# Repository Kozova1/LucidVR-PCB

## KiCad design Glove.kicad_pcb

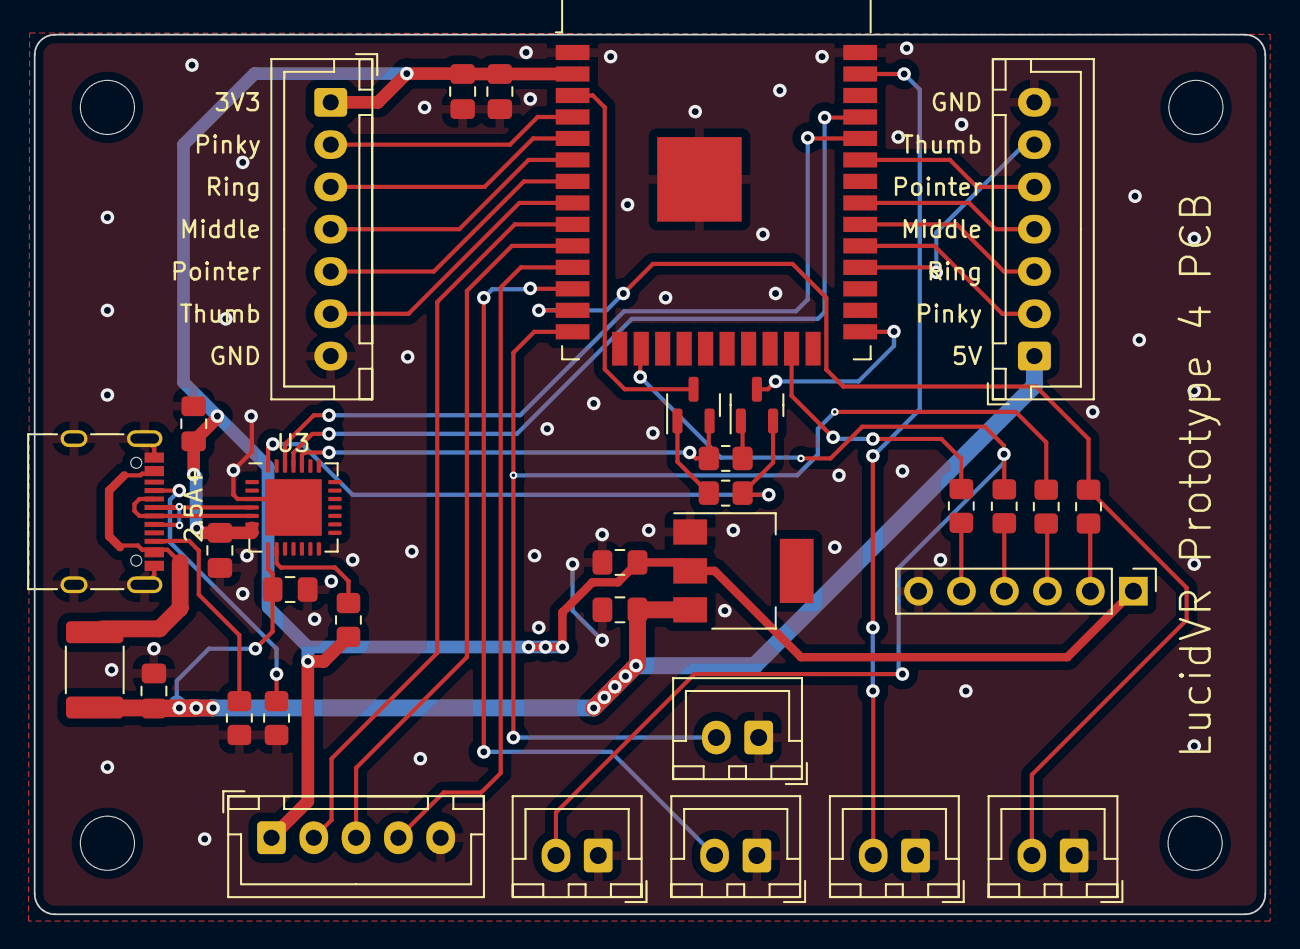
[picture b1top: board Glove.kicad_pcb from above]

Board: 2 copper layers, 72.8 x 52.0 mm, 33 parts (0 on the bottom side), 40 nets.

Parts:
BTN_A1: Button A; JST_XH_B2B-XH-A_1x02_P2.50mm_Vertical
BTN_B1: Button B; JST_XH_B2B-XH-A_1x02_P2.50mm_Vertical
BTN_Grab1: Grab; JST_XH_B2B-XH-A_1x02_P2.50mm_Vertical
BTN_Pinch1: Pinch; JST_XH_B2B-XH-A_1x02_P2.50mm_Vertical
BTN_Trigger1: Trigger; JST_XH_B2B-XH-A_1x02_P2.50mm_Vertical
C1, C4: 10uF; C_0805_2012Metric_Pad1.18x1.45mm_HandSolder
C2, C3, C5: 0.1uF; C_0805_2012Metric_Pad1.18x1.45mm_HandSolder
C6: 4.7uF; C_0805_2012Metric_Pad1.18x1.45mm_HandSolder
C_In1: 10uF; C_0805_2012Metric_Pad1.18x1.45mm_HandSolder
C_Out1: 10uF; C_0805_2012Metric_Pad1.18x1.45mm_HandSolder
F1: 3.5A; Fuse_1812_4532Metric_Pad1.30x3.40mm_HandSolder
J1: USB_C_Receptacle_USB2.0; USB_C_Receptacle_XKB_U262-16XN-4BVC11
J2: Joystick; JST_XH_B5B-XH-A_1x05_P2.50mm_Vertical
J3, J4: Conn_01x07; JST_XH_B7B-XH-A_1x07_P2.50mm_Vertical
J5: Conn_01x06; PinHeader_1x06_P2.54mm_Vertical
Q1, Q2: 2N7002; SOT-23
R1, R2: 5.1k; R_0805_2012Metric_Pad1.20x1.40mm_HandSolder
R3, R8: 10k; R_0805_2012Metric_Pad1.20x1.40mm_HandSolder
R4, R5, R6, R7: 100; R_0805_2012Metric_Pad1.20x1.40mm_HandSolder
R9: 1k; R_0805_2012Metric_Pad1.20x1.40mm_HandSolder
U1: LM1117S-3.3; SOT-223
U2: ESP32-WROOM-32D; ESP32-WROOM-32
U3: CP2102N-Axx-xQFN28; QFN-28-1EP_5x5mm_P0.5mm_EP3.35x3.35mm

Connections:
+3V3: C1.1, C2.1, C4.1, C5.1, C_Out1.1, J2.1, J4.1, J5.1, R9.1, U1.2 (VO), U2.2 (VDD), U3.6 (VDD), U3.7 (VREGIN)
+5V: C3.2, C6.2, C_In1.1, F1.2, J3.1, U1.3 (VI), U3.8 (VBUS)
/D+: J1.A6 (D+), J1.B6 (D+), U3.4 (D+)
/D-: J1.A7 (D-), J1.B7 (D-), U3.5 (D-)
/MTCK: J5.4, R6.2
/MTDI: J5.3, R5.2
/MTDO: J5.5, R7.2
/MTMS: J5.2, R4.2
BtnA: BTN_A1.2, U2.12 (IO27)
BtnB: BTN_B1.2, R4.1, U2.13 (IO14)
BtnGrab: BTN_Grab1.2, R6.1, U2.16 (IO13)
BtnPinch: BTN_Pinch1.2, U2.37 (IO23)
BtnTrigger: BTN_Trigger1.2, R5.1, U2.14 (IO12)
EN: Q1.3 (D), U2.3 (EN)
GND: BTN_A1.1, BTN_B1.1, BTN_Grab1.1, BTN_Pinch1.1, BTN_Trigger1.1, C1.2, C2.2, C3.1, C4.2, C5.2, C6.1, C_In1.2, C_Out1.2, J1.A1 (GND), J1.A12 (GND), J1.B1 (GND), J1.B12 (GND), J1.S1 (SHIELD), J2.5, J3.7, J4.7, J5.6, R1.2, R2.2, U1.1 (GND), U2.1 (GND), U2.15 (GND), U2.38 (GND), U2.39 (GND), U3.3 (GND), U3.29 (GND)
IO0: Q2.3 (D), U2.25 (IO0)
JTAG_MTDO: R7.1, U2.23 (IO15)
JoyClick: J2.4, U2.11 (IO26)
JoyX: J2.2, U2.9 (IO33)
JoyY: J2.3, U2.10 (IO25)
MiddlePWM: J3.4, U2.31 (IO19)
MiddlePot: J4.4, U2.6 (IO34)
unnamed: F1.1, J1.A4 (VBUS), J1.A9 (VBUS), J1.B4 (VBUS), J1.B9 (VBUS)
unnamed: J1.A5 (CC1), R2.1
unnamed: J1.B5 (CC2), R1.1
unnamed: Q1.1 (G), R8.1
unnamed: Q1.2 (S), R3.1, U3.24 (~RTS)
unnamed: Q2.1 (G), R3.2
unnamed: Q2.2 (S), R8.2, U3.28 (~DTR)
unnamed: R9.2, U3.9 (~RST)
PinkyPWM: J3.2, U2.29 (IO5)
PinkyPot: J4.2, U2.4 (SENSOR_VP)
PointerPWM: J3.5, U2.33 (IO21)
PointerPot: J4.5, U2.7 (IO35)
RXD: U2.35 (TXD0/IO1), U3.25 (RXD)
RingPWM: J3.3, U2.30 (IO18)
RingPot: J4.3, U2.5 (SENSOR_VN)
TXD: U2.34 (RXD0/IO3), U3.26 (TXD)
ThumbPWM: J3.6, U2.28 (IO17)
ThumbPot: J4.6, U2.8 (IO32)

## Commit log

2022-04-06 Remove Voltage Divider from Power Supply
2022-04-06 Connect VIO to 3.3v for CP2102 chip
2022-04-06 Add 5.1k Pulldown for CC1 and CC2
2022-04-06 Remove in-pad vias and add 1k pullup for CP2102 RST
2022-04-06 Remove CHECK VCC silkscreen
2022-04-06 Move decoupling capacitors
2022-04-07 Route D- and D+ as differential pair
2022-04-07 Add 4th screw hole and branding
2022-04-08 Fix routing, move capacitors closer to ICs
2022-04-08 Connect all servos and potentiometers in parallel
    This saves a bunch of board space.
2022-04-11 Add massive changes to routing
2022-04-11 Sprinkled in some GND vias
2022-04-18 Widen 3v3 trace, remove unneeded 2 middle layers
2022-04-22 Change routing of 5V and 3V3 lines
2022-04-23 Switch to QFN28 version of CP2102
2022-04-24 Remove In1.Cu and In2.Cu layers
